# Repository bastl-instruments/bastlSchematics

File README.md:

# bastlSchematics
all hw design schematics in one place
license CC-BY-SA

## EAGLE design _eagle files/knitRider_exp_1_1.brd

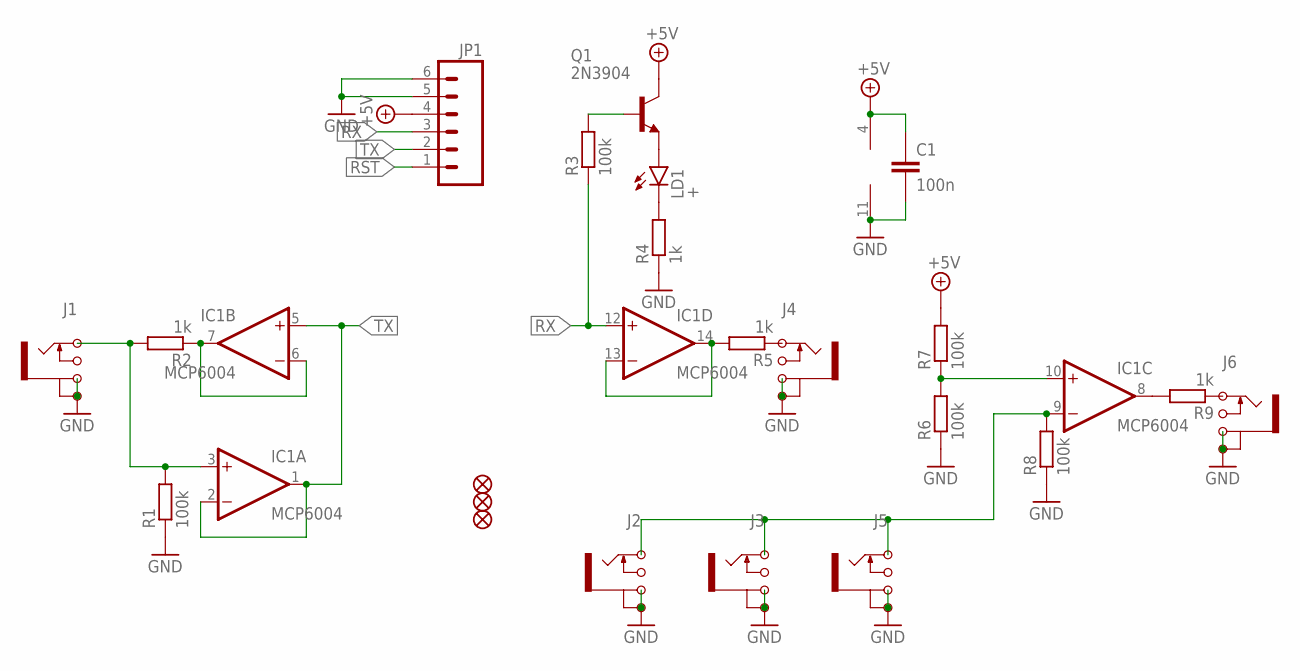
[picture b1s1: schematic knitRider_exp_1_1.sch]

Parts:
C1: 100n; CAPACITOR0603
FID1, FID2, FID3: FIDUCIAL
IC1: MCP6004; SO14
J1, J2, J3, J4, J5, J6: JACK_MONOJACK_MONO; JACK_MONO
JP1: M06LOCK; 1X06_LOCK
LD1: +; LEDSMALLHOLES
Q1: 2N3904; SOT23
R1, R3, R6, R7, R8: 100k; RESISTOR0603
R2, R4, R5, R9: 1k; RESISTOR0603

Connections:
+5V: C1.1, IC1.4 (V+), JP1.4, Q1.C, R7.2
GND: C1.2, IC1.11 (V-), J1.G1, J1.G2, J2.G1, J2.G2, J3.G1, J3.G2, J4.G1, J4.G2, J5.G1, J5.G2, J6.G1, J6.G2, JP1.5, JP1.6, R1.1, R4.1, R6.1, R8.1
unnamed: LD1.A, Q1.E
unnamed: Q1.B, R3.2
unnamed: J6.T, R9.1
unnamed: J4.T, R5.1
unnamed: IC1.6 (-IN), IC1.7 (OUT), R2.1
unnamed: IC1.9 (-IN), J2.T, J3.T, J5.T, R8.2
unnamed: IC1.10 (+IN), R6.2, R7.1
unnamed: LD1.K (C), R4.2
unnamed: IC1.3 (+IN), J1.T, R1.2, R2.2
unnamed: IC1.8 (OUT), R9.2
unnamed: IC1.13 (-IN), IC1.14 (OUT), R5.2
RST: JP1.1
RX: IC1.12 (+IN), JP1.3, R3.1
TX: IC1.1 (OUT), IC1.2 (-IN), IC1.5 (+IN), JP1.2

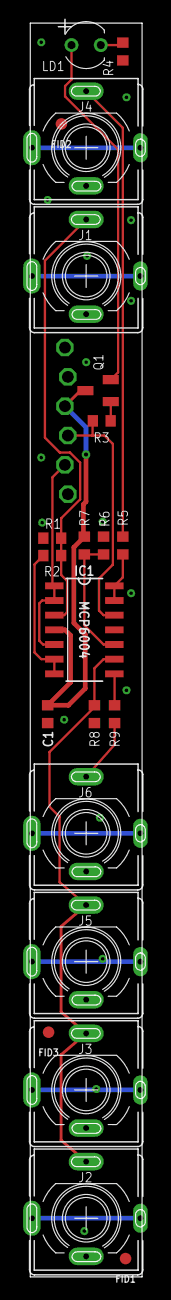
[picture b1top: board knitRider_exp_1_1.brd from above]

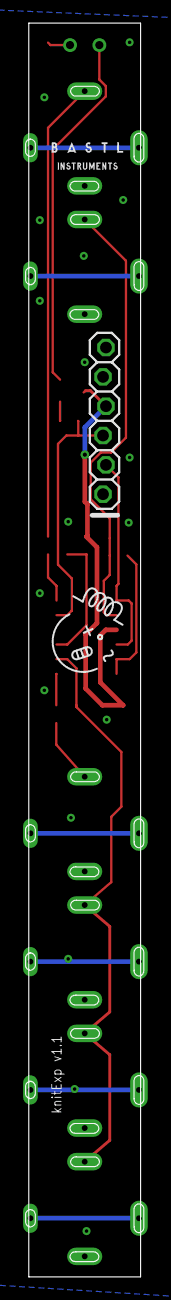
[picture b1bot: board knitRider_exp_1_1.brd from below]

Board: 2 copper layers, 10.2 x 108.6 mm, 25 parts (3 on the bottom side), 15 nets.

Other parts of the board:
U$1: BASTL_HLAVA_1
U$2: BASTL_LOGO_1

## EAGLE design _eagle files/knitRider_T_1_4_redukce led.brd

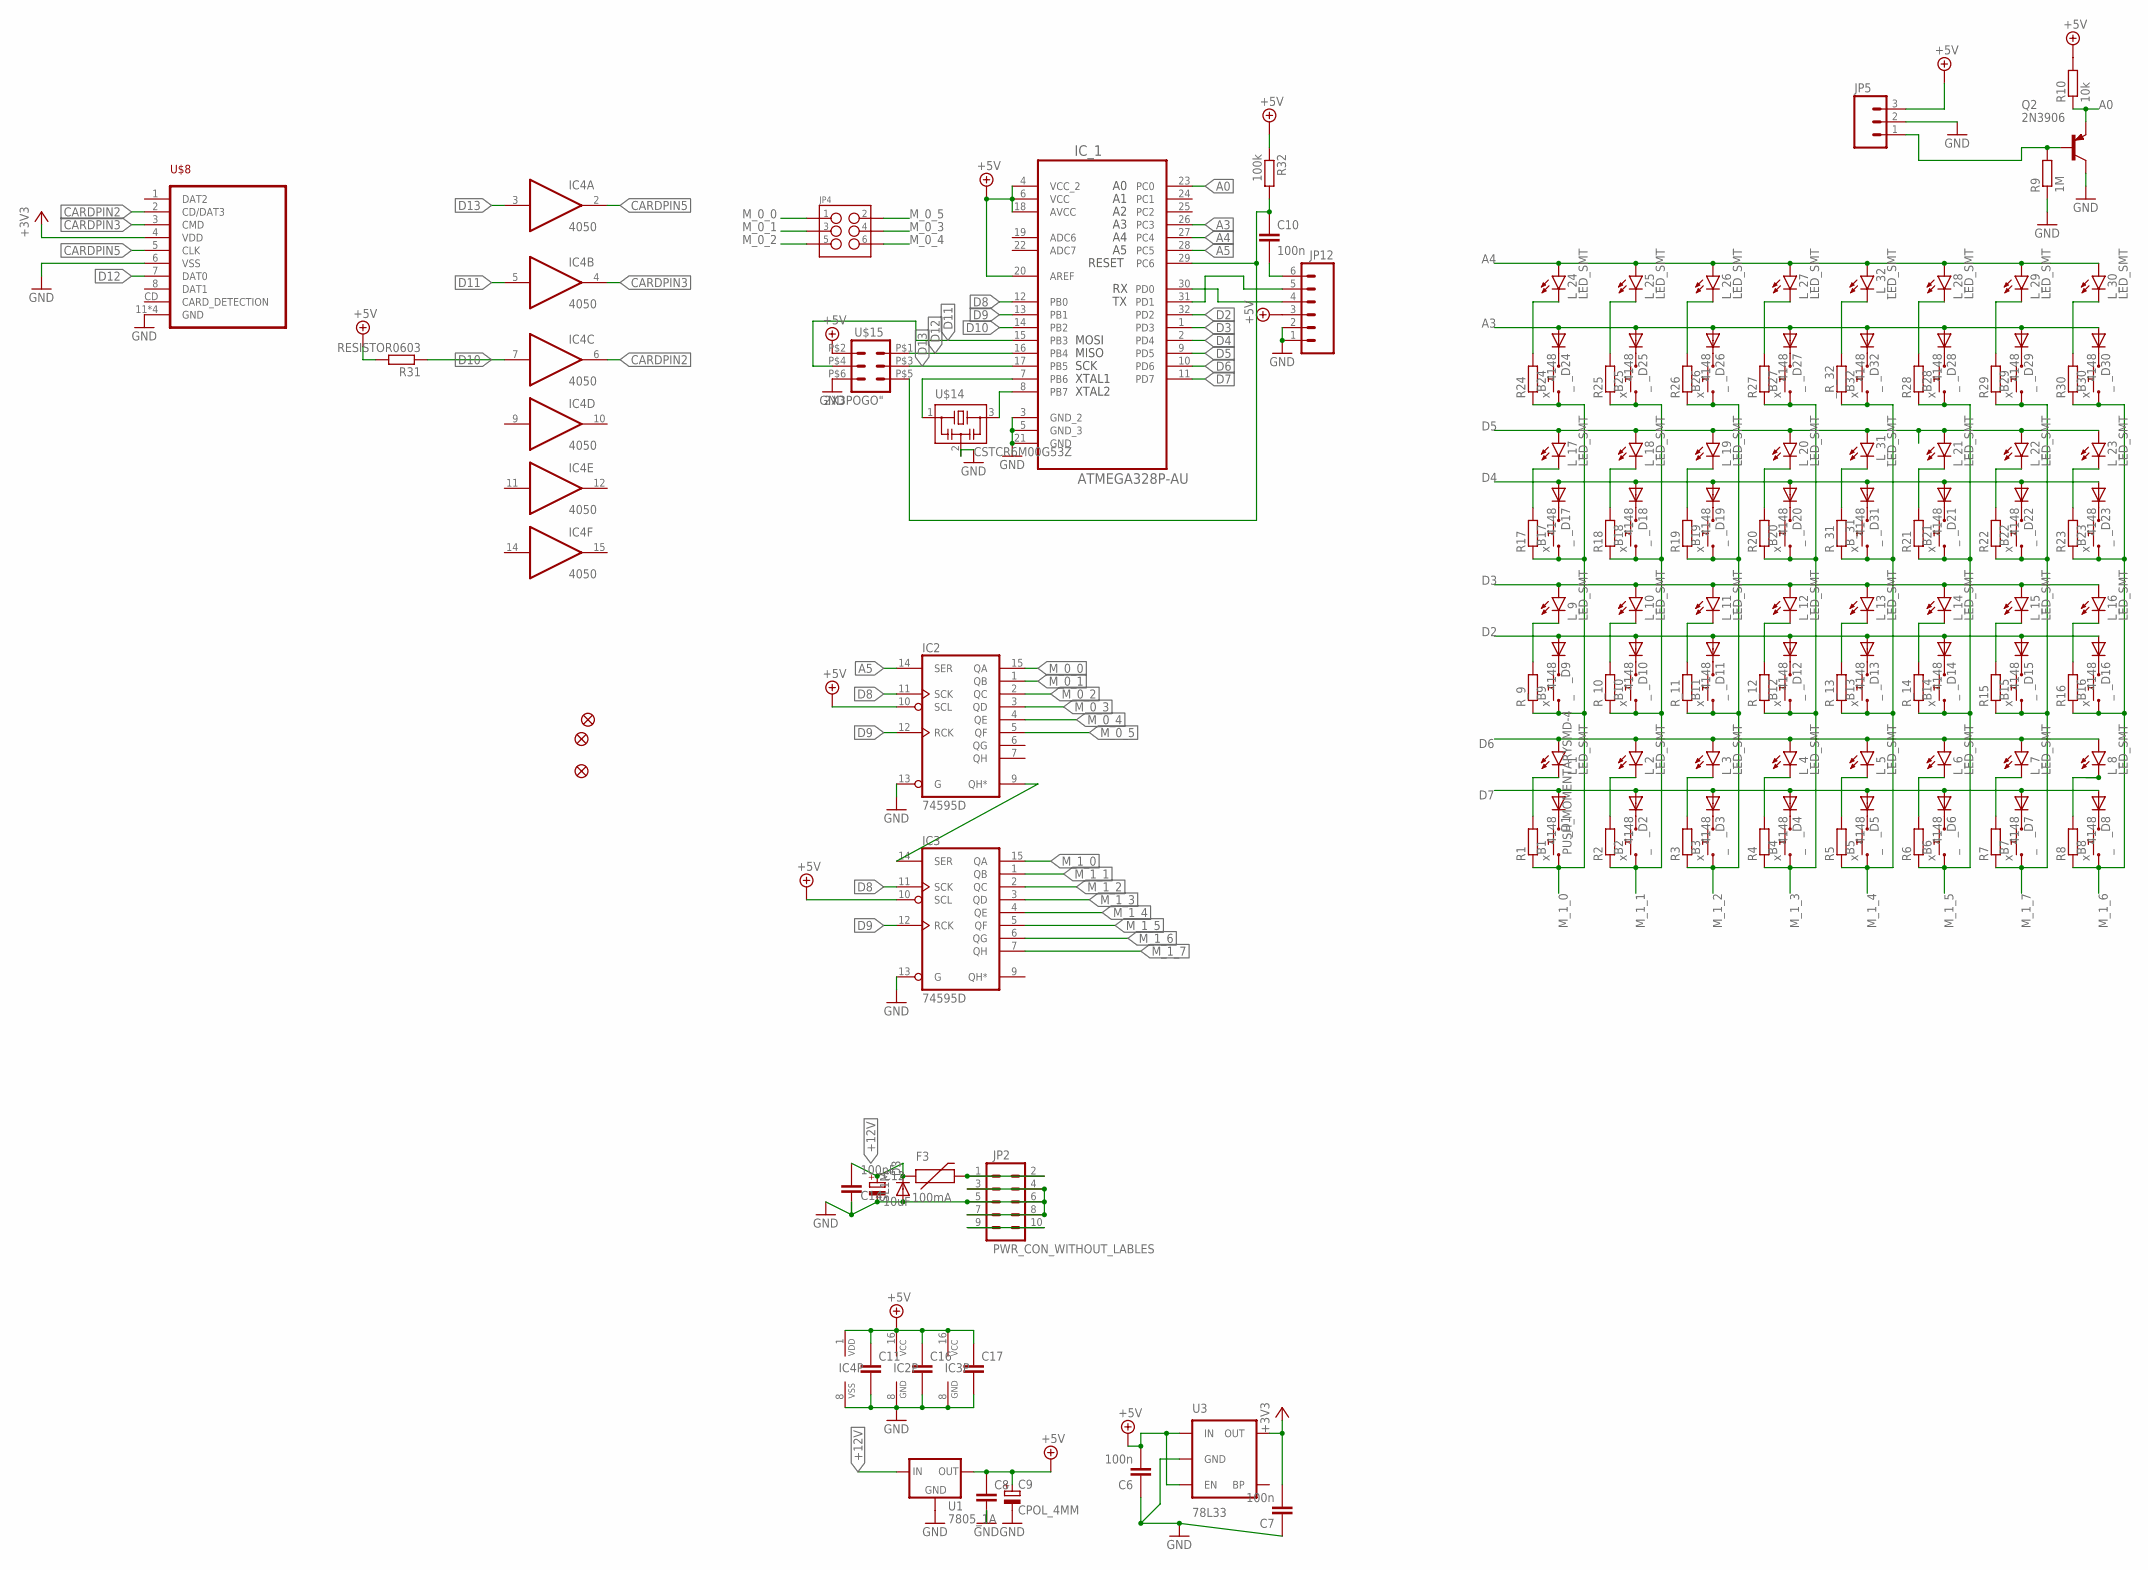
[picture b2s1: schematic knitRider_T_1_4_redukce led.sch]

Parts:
B1: PUSH_MOMENTARYSMD-4; TACTILE_SWITCH_TALL
B2, B3, B4, B5, B6, B7, B8, B9, B10, B11, B12, B13, B14, B15, B16, B17, B18, B19, B20, B21, B22, B23, B24, B25, B26, B27, B28, B29, B30, B32: _; TACTILE_SWITCH_TALL
B_31: _; TACTILE_SWITCH_TALL
C6, C7, C10: 100n; CAPACITOR0603
C8, C11, C16, C17: CAPACITOR0603
C9: CPOL_4MM
C12: 10uF; CPOL_4MM
C14: 100nF; CAPACITOR0603
D3: SL1M; SOD123
F3: 100mA; PTC0805
FID1, FID2, FID3: FIDUCIAL
IC2, IC3: 74595D; SO16
IC4: 4050; SO16
IC_1: ATMEGA328P-AU; TQFP32
JP2: PWR_CON_WITHOUT_LABLES
JP4: M03X2NO_SILK; 2X3-NS
JP5: M03LOCK; 1X03_LOCK
JP12: M06LOCK; 1X06_LOCK
L_1, L_2, L_3, L_4, L_5, L_6, L_7, L_8, L_9, L_10, L_11, L_12, L_13, L_14, L_15, L_16, L_17, L_18, L_19, L_20, L_21, L_22, L_23, L_24, L_25, L_26, L_27, L_28, L_29, L_30: LED_SMT; LED_0603
Q2: 2N3906; SOT23
R1, R2, R3, R4, R5, R6, R7, R8, R15, R16, R17, R18, R19, R20, R21, R22, R23, R24, R25, R26, R27, R28, R29, R30: x; RESISTOR0603
R9: 1M; RESISTOR0603
R10: 10k; RESISTOR0603
R31: RESISTOR0603
R32: 100k; RESISTOR0603
R_9, R_10, R_11, R_12, R_13, R_14, R_31: x; RESISTOR0603
U1: 7805_1A; DPAK
U3: 78L33; SOT23-5
U$8: SD_CARD_SLOT; MICRO_SD_CARD_SLOT
U$14: CSTCR6M00G53Z; CSTCR6M
U$15: 2X3POGO"; 2X3_POGO
_D1, _D2, _D3, _D4, _D5, _D6, _D7, _D8, _D9, _D10, _D11, _D12, _D13, _D14, _D15, _D16, _D17, _D18, _D19, _D20, _D21, _D22, _D23, _D24, _D25, _D26, _D27, _D28, _D29, _D30, _D31, _D32: 4148; DIODE_0603
_L_31, _L_32: LED_SMT; LED_0603
_R_32: x; RESISTOR0603

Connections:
+3V3: C7.2, U3.5 (OUT), U$8.4 (VDD)
+5V: C6.2, C8.1, C9.+, C11.1, C16.1, C17.1, IC2.10 (SCL), IC2.16 (VCC), IC3.10 (SCL), IC3.16 (VCC), IC4.1 (VDD), IC_1.4 (VCC_2), IC_1.6 (VCC), IC_1.18 (AVCC), IC_1.20 (AREF), JP5.3, JP12.3, R10.2, R31.2, R32.1, U1.3 (OUT), U3.1 (IN), U3.3 (EN), U$15.P$2 (2)
+12V: C12.+, C14.2, D3.C, F3.2 (1), U1.1 (IN)
A0: IC_1.23 (PC0), Q2.E, R10.1
A3: IC_1.26 (PC3), _D24.A, _D25.A, _D26.A, _D27.A, _D28.A, _D29.A, _D30.A, _D32.A
A4: IC_1.27 (PC4), L_24.A, L_25.A, L_26.A, L_27.A, L_28.A, L_29.A, L_30.A, _L_32.A
A5: IC2.14 (SER), IC_1.28 (PC5)
CARDPIN2: IC4.6 (O), U$8.2 (CD/DAT3)
CARDPIN3: IC4.4 (O), U$8.3 (CMD)
CARDPIN5: IC4.2 (O), U$8.5 (CLK)
D2: IC_1.32 (PD2), _D9.A, _D10.A, _D11.A, _D12.A, _D13.A, _D14.A, _D15.A, _D16.A
D3: IC_1.1 (PD3), L_9.A, L_10.A, L_11.A, L_12.A, L_13.A, L_14.A, L_15.A, L_16.A
D4: IC_1.2 (PD4), _D17.A, _D18.A, _D19.A, _D20.A, _D21.A, _D22.A, _D23.A, _D31.A
D5: IC_1.9 (PD5), L_17.A, L_18.A, L_19.A, L_20.A, L_21.A, L_22.A, L_23.A, _L_31.A
D6: IC_1.10 (PD6), L_1.A, L_2.A, L_3.A, L_4.A, L_5.A, L_6.A, L_7.A, L_8.A
D7: IC_1.11 (PD7), _D1.A, _D2.A, _D3.A, _D4.A, _D5.A, _D6.A, _D7.A, _D8.A
D8: IC2.11 (SCK), IC3.11 (SCK), IC_1.12 (PB0)
D9: IC2.12 (RCK), IC3.12 (RCK), IC_1.13 (PB1)
D10: IC4.7 (I), IC_1.14 (PB2), R31.1
D11: IC4.5 (I), IC_1.15 (PB3), U$15.P$4 (4)
D12: IC_1.16 (PB4), U$8.7 (DAT0), U$15.P$1 (1)
D13: IC4.3 (I), IC_1.17 (PB5), U$15.P$3 (3)
GND: C6.1, C7.1, C8.2, C9.-, C11.2, C12.-, C14.1, C16.2, C17.2, D3.A, IC2.8 (GND), IC2.13 (G), IC3.8 (GND), IC3.13 (G), IC4.8 (VSS), IC_1.3 (GND_2), IC_1.5 (GND_3), IC_1.21 (GND), JP2.3, JP2.4, JP2.5, JP2.6, JP2.7, JP2.8, JP5.2, JP12.1, JP12.2, Q2.C, R9.1, U1.4 (GND), U3.2 (GND), U$8.6 (VSS), U$8.11 (GND), U$8.12 (GND), U$8.13 (GND), U$8.G (GND), U$14.2, U$15.P$6 (6)
L32: R_31.2, _L_31.K (C)
M_0_0: IC2.15 (QA), JP4.1
M_0_1: IC2.1 (QB), JP4.3
M_0_2: IC2.2 (QC), JP4.5
M_0_3: IC2.3 (QD), JP4.4
M_0_4: IC2.4 (QE), JP4.6
M_0_5: IC2.5 (QF), JP4.2
M_1_0: B1.A1 (1), B1.A2 (1), B9.A1 (1), B9.A2 (1), B17.A1 (1), B17.A2 (1), B24.A1 (1), B24.A2 (1), IC3.15 (QA), R1.1, R17.1, R24.1, R_9.1
M_1_1: B2.A1 (1), B2.A2 (1), B10.A1 (1), B10.A2 (1), B18.A1 (1), B18.A2 (1), B25.A1 (1), B25.A2 (1), IC3.1 (QB), R2.1, R18.1, R25.1, R_10.1
M_1_2: B3.A1 (1), B3.A2 (1), B11.A1 (1), B11.A2 (1), B19.A1 (1), B19.A2 (1), B26.A1 (1), B26.A2 (1), IC3.2 (QC), R3.1, R19.1, R26.1, R_11.1
M_1_3: B4.A1 (1), B4.A2 (1), B12.A1 (1), B12.A2 (1), B20.A1 (1), B20.A2 (1), B27.A1 (1), B27.A2 (1), IC3.3 (QD), R4.1, R20.1, R27.1, R_12.1
M_1_4: B5.A1 (1), B5.A2 (1), B13.A1 (1), B13.A2 (1), B32.A1 (1), B32.A2 (1), B_31.A1 (1), B_31.A2 (1), IC3.4 (QE), R5.1, R_13.1, R_31.1, _R_32.1
M_1_5: B6.A1 (1), B6.A2 (1), B14.A1 (1), B14.A2 (1), B21.A1 (1), B21.A2 (1), B28.A1 (1), B28.A2 (1), IC3.5 (QF), R6.1, R21.1, R28.1, R_14.1
M_1_6: B8.A1 (1), B8.A2 (1), B16.A1 (1), B16.A2 (1), B23.A1 (1), B23.A2 (1), B30.A1 (1), B30.A2 (1), IC3.6 (QG), R8.1, R16.1, R23.1, R30.1
M_1_7: B7.A1 (1), B7.A2 (1), B15.A1 (1), B15.A2 (1), B22.A1 (1), B22.A2 (1), B29.A1 (1), B29.A2 (1), IC3.7 (QH), R7.1, R15.1, R22.1, R29.1
unnamed: B1.B1 (2), B1.B2 (2), _D1.K (C)
unnamed: B2.B1 (2), B2.B2 (2), _D2.K (C)
unnamed: B3.B1 (2), B3.B2 (2), _D3.K (C)
unnamed: JP5.1, Q2.B, R9.2
unnamed: B4.B1 (2), B4.B2 (2), _D4.K (C)
unnamed: B5.B1 (2), B5.B2 (2), _D5.K (C)
unnamed: B6.B1 (2), B6.B2 (2), _D6.K (C)
unnamed: L_3.K (C), R3.2
unnamed: F3.3 (2), JP2.1, JP2.2
unnamed: B9.B1 (2), B9.B2 (2), _D9.K (C)
unnamed: B10.B1 (2), B10.B2 (2), _D10.K (C)
unnamed: B7.B1 (2), B7.B2 (2), _D7.K (C)
unnamed: B8.B1 (2), B8.B2 (2), _D8.K (C)
unnamed: JP2.9, JP2.10
unnamed: B11.B1 (2), B11.B2 (2), _D11.K (C)
unnamed: L_4.K (C), R4.2
unnamed: L_5.K (C), R5.2
unnamed: L_6.K (C), R6.2
unnamed: L_7.K (C), R7.2
unnamed: B12.B1 (2), B12.B2 (2), _D12.K (C)
unnamed: L_8.K (C), R8.2
unnamed: B13.B1 (2), B13.B2 (2), _D13.K (C)
unnamed: B14.B1 (2), B14.B2 (2), _D14.K (C)
unnamed: B15.B1 (2), B15.B2 (2), _D15.K (C)
unnamed: B16.B1 (2), B16.B2 (2), _D16.K (C)
unnamed: B17.B1 (2), B17.B2 (2), _D17.K (C)
unnamed: B18.B1 (2), B18.B2 (2), _D18.K (C)
unnamed: B19.B1 (2), B19.B2 (2), _D19.K (C)
unnamed: L_1.K (C), R1.2
unnamed: L_2.K (C), R2.2
unnamed: B20.B1 (2), B20.B2 (2), _D20.K (C)
unnamed: B21.B1 (2), B21.B2 (2), _D21.K (C)
unnamed: B22.B1 (2), B22.B2 (2), _D22.K (C)
unnamed: B23.B1 (2), B23.B2 (2), _D23.K (C)
unnamed: B24.B1 (2), B24.B2 (2), _D24.K (C)
unnamed: L_9.K (C), R_9.2
unnamed: L_10.K (C), R_10.2
unnamed: L_11.K (C), R_11.2
unnamed: L_12.K (C), R_12.2
unnamed: L_13.K (C), R_13.2
unnamed: L_14.K (C), R_14.2
unnamed: L_15.K (C), R15.2
unnamed: L_16.K (C), R16.2
unnamed: B25.B1 (2), B25.B2 (2), _D25.K (C)
unnamed: B26.B1 (2), B26.B2 (2), _D26.K (C)
unnamed: L_18.K (C), R18.2
unnamed: L_19.K (C), R19.2
unnamed: L_17.K (C), R17.2
unnamed: L_20.K (C), R20.2
unnamed: L_23.K (C), R23.2
unnamed: L_22.K (C), R22.2
unnamed: B27.B1 (2), B27.B2 (2), _D27.K (C)
unnamed: L_21.K (C), R21.2
unnamed: B28.B1 (2), B28.B2 (2), _D28.K (C)
unnamed: B29.B1 (2), B29.B2 (2), _D29.K (C)
unnamed: B30.B1 (2), B30.B2 (2), _D30.K (C)
unnamed: B_31.B1 (2), B_31.B2 (2), _D31.K (C)
unnamed: B32.B1 (2), B32.B2 (2), _D32.K (C)
unnamed: IC2.9 (QH*), IC3.14 (SER)
unnamed: L_24.K (C), R24.2
unnamed: L_25.K (C), R25.2
unnamed: L_26.K (C), R26.2
unnamed: L_27.K (C), R27.2
unnamed: L_28.K (C), R28.2
unnamed: L_29.K (C), R29.2
unnamed: L_30.K (C), R30.2
unnamed: IC_1.7 (PB6), U$14.1
unnamed: IC_1.8 (PB7), U$14.3
unnamed: IC_1.30 (PD0), JP12.4
unnamed: IC_1.31 (PD1), JP12.5
unnamed: C10.1, IC_1.29 (PC6), R32.2, U$15.P$5 (5)
unnamed: C10.2, JP12.6
_L32: _L_32.K (C), _R_32.2

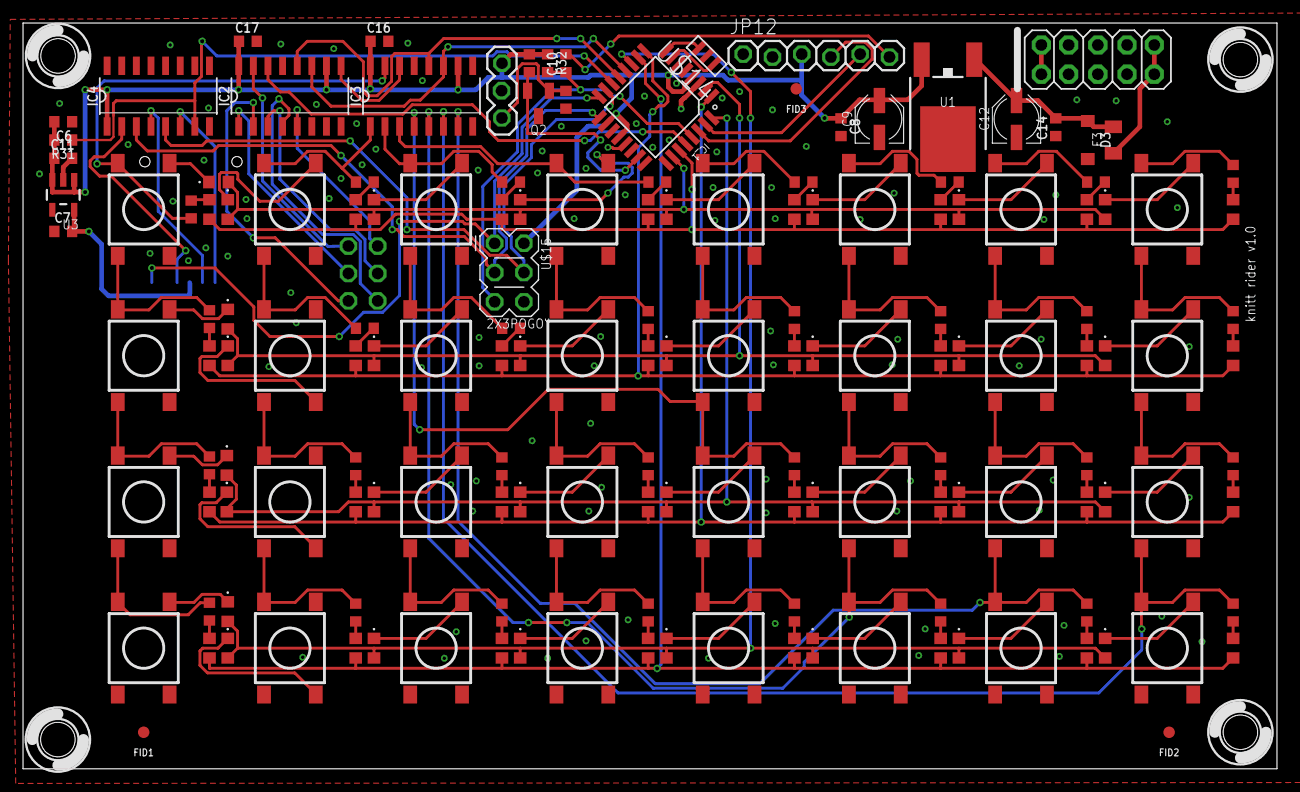
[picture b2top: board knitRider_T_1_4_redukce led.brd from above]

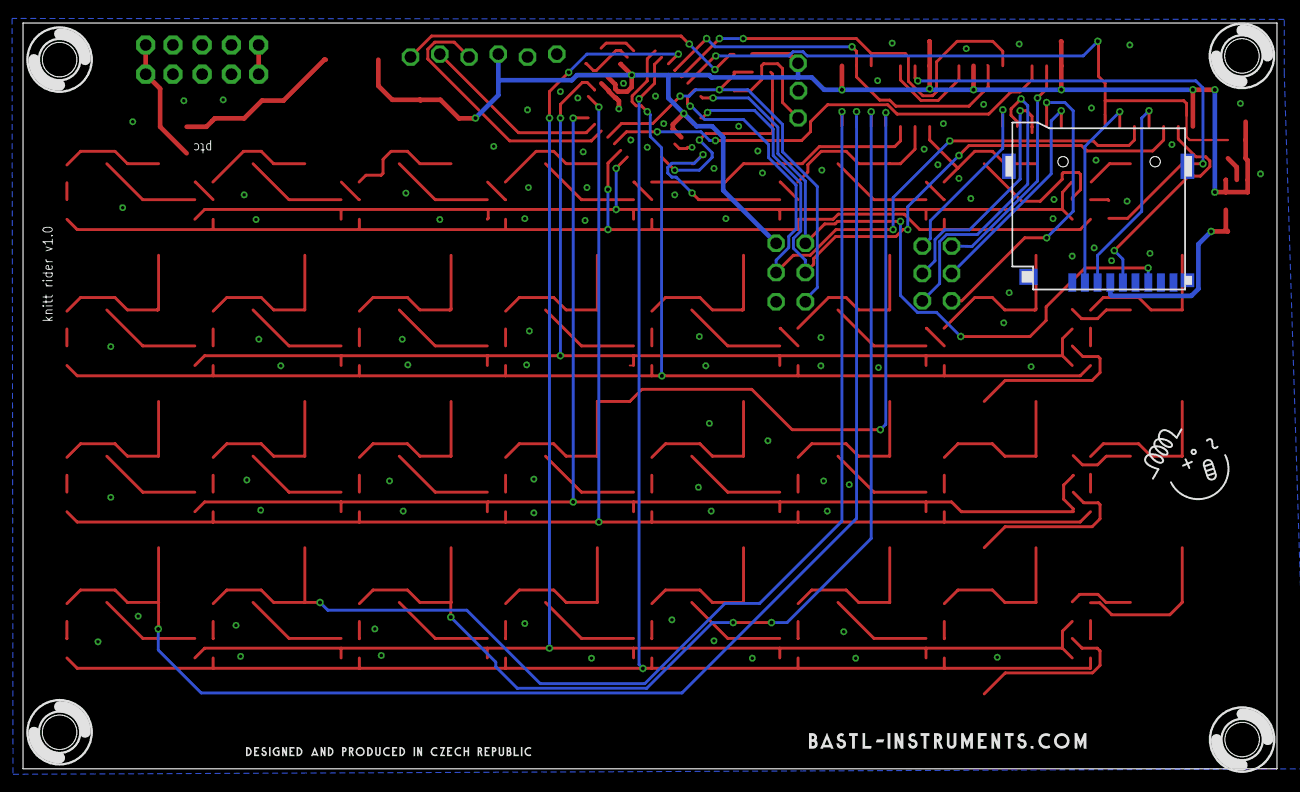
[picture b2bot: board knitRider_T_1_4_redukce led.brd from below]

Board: 2 copper layers, 108.9 x 64.8 mm, 168 parts (4 on the bottom side), 111 nets.

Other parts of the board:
U$1: BASTL_WEB_2
U$2, U$3, U$4, U$5: 3MM_HOLE
U$6: DES_PROD
U$11: BASTL_HLAVA_1

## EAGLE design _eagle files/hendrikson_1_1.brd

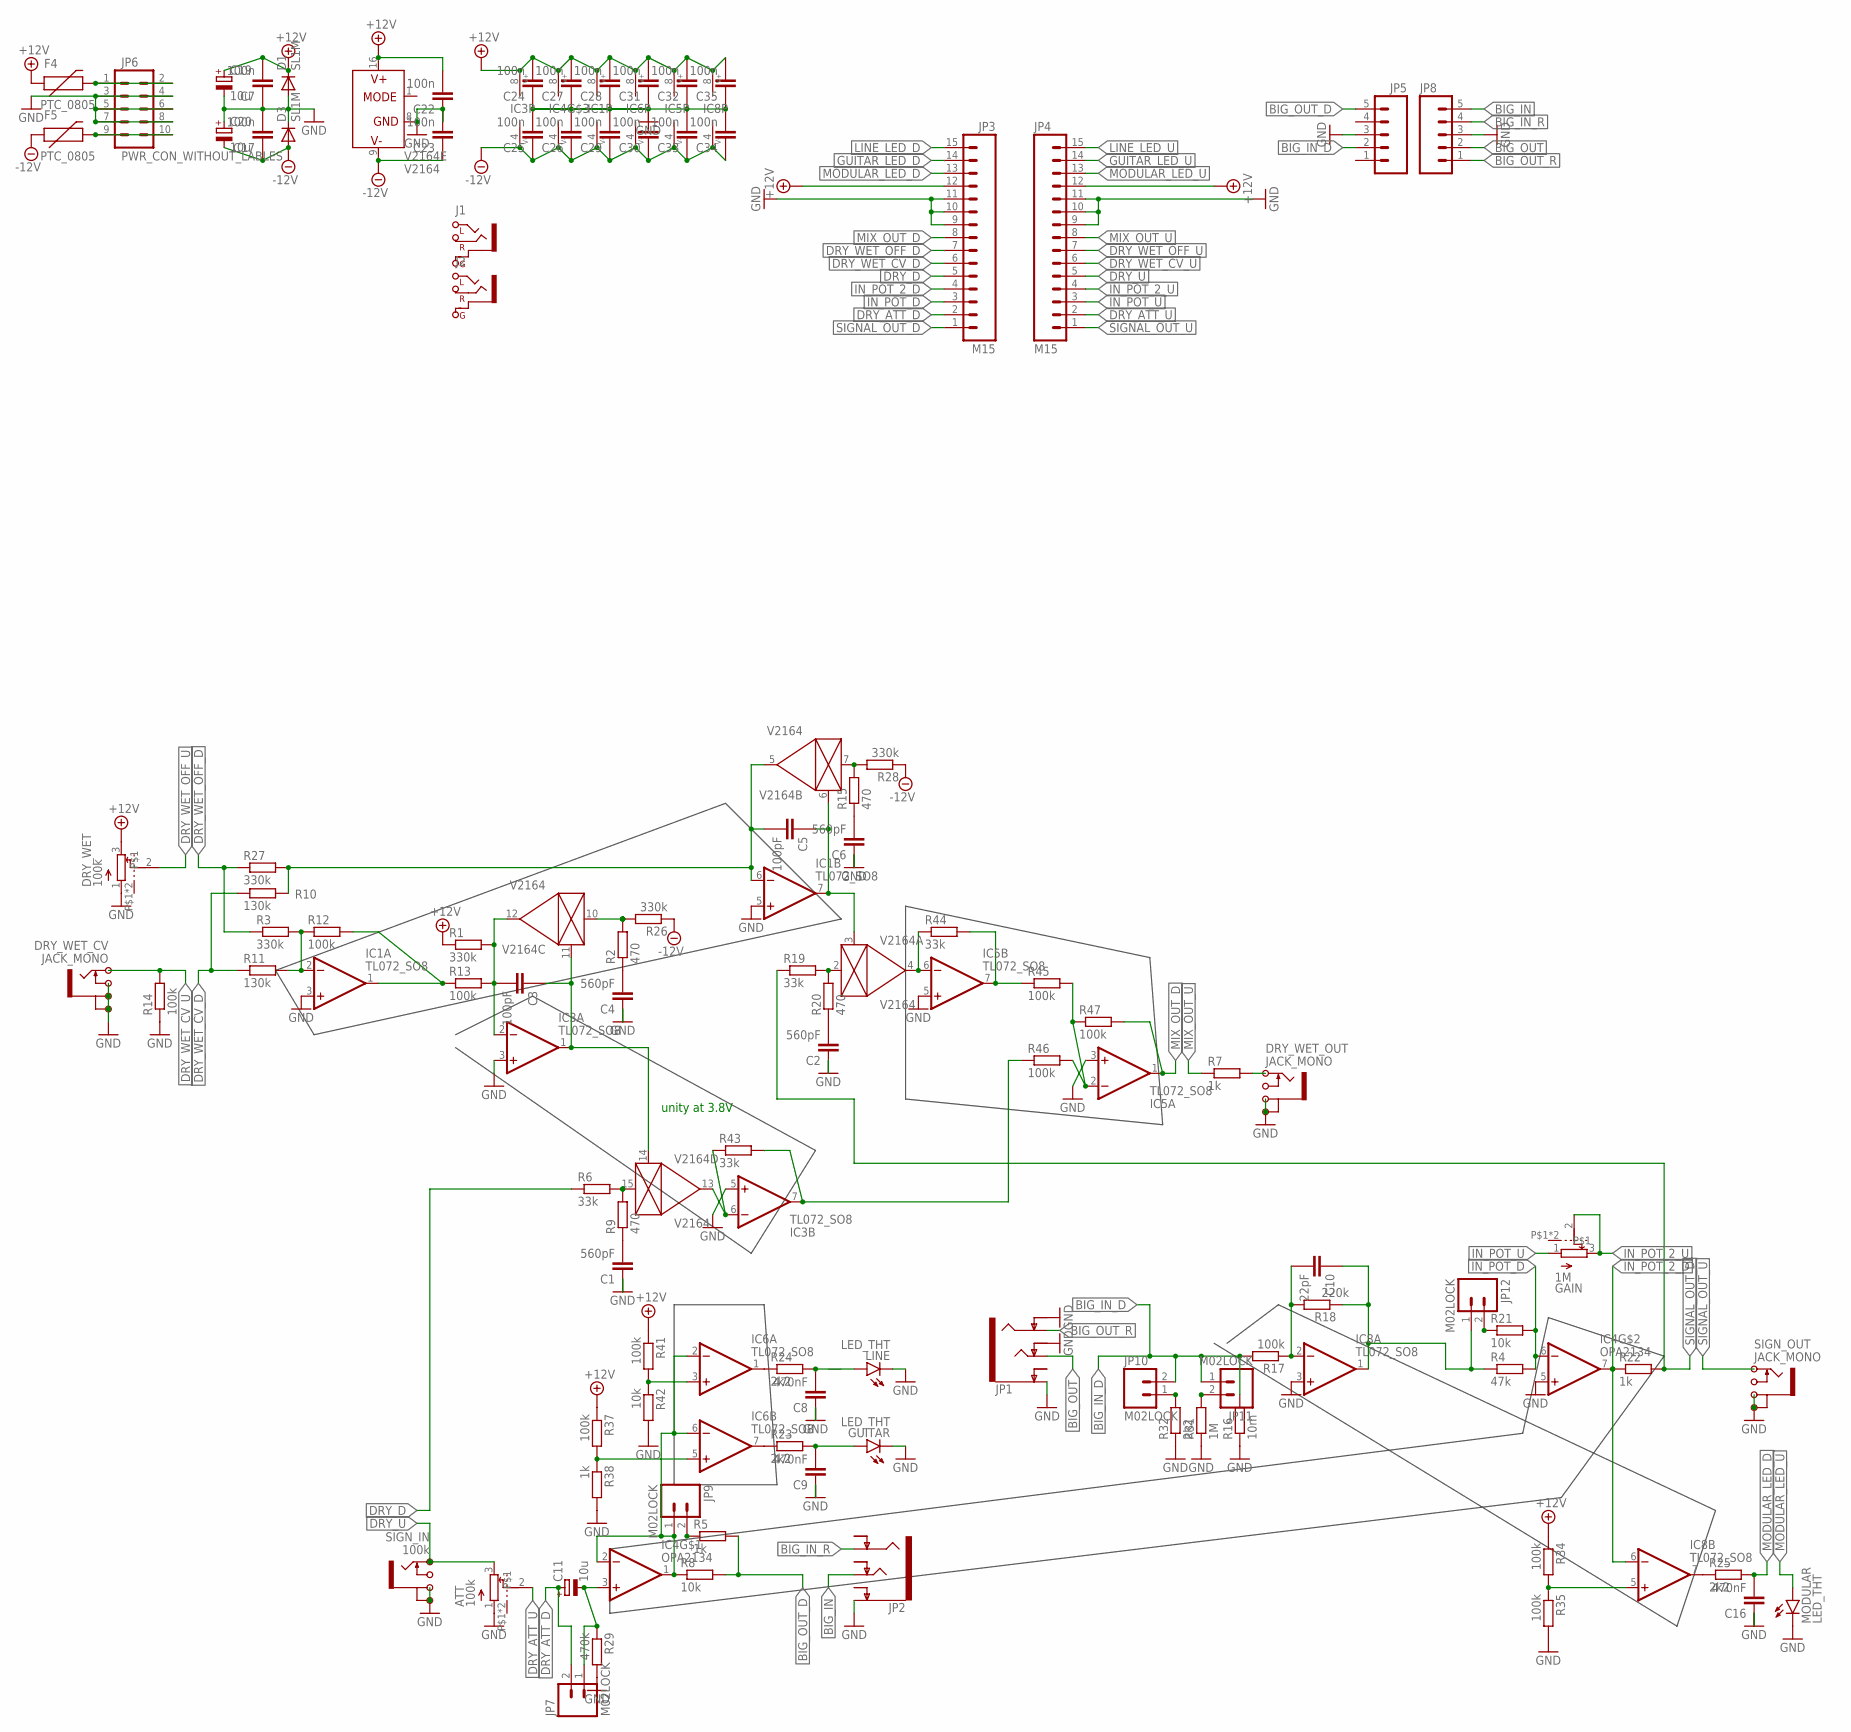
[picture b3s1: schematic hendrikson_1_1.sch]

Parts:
ATT: 100k; POT_ALPHA
C1, C2, C4, C6: 560pF; CAPACITOR0603
C3, C5: 100pF; CAPACITOR0603
C7, C17, C22, C23, C24, C25, C26, C27, C28, C29, C30, C31, C32, C33, C34, C35: 100n; CAPACITOR0603
C8, C9, C16: 470nF; CAPACITOR0603
C10: 22pF; CAPACITOR0603
C11, C19, C20: 10u; CPOL_4MM
D1, D3: SL1M; SOD123
DRY_WET: 100k; POT_ALPHA
DRY_WET_CV: JACK_MONO
DRY_WET_OUT: JACK_MONO
F4, F5: PTC_0805; PTC0805
GAIN: 1M; POT_ALPHA
GUITAR: LED_THT; LEDSMALLHOLES
IC1, IC3, IC5, IC6, IC8: TL072_SO8; SO8
IC4: OPA2134; SO8
J1, J2: NEUTRIK_VERT_JACK_6.3MM; RJ5VM
JP1, JP2: SPARKFUN-CONNECTORS_AUDIO-JACK4-.25-HORIZ-TRS; SPARKFUN-CONNECTORS_AUDIO-JACK-.25-INCH-HORIZ-PTH
JP3, JP4: M15; 1X15
JP5: M05PTH; 1X05
JP6: PWR_CON_WITHOUT_LABLES
JP7, JP9, JP10, JP11, JP12: M02LOCK; 1X02_LOCK
JP8: M05PTH_LONGPADS; 1X05_LONGPADS
LINE: LED_THT; LEDSMALLHOLES
MODULAR: LED_THT; LEDSMALLHOLES
R1, R3, R26, R27, R28: 330k; RESISTOR0603
R2, R9, R15, R20: 470; RESISTOR0603
R4: 47k; RESISTOR0603
R5, R7, R22, R38: 1k; RESISTOR0603
R6, R19, R43, R44: 33k; RESISTOR0603
R8, R21, R42: 10k; RESISTOR0603
R10, R11: 130k; RESISTOR0603
R12, R13, R14, R17, R34, R35, R37, R41, R45, R46, R47: 100k; RESISTOR0603
R16: 10m; RESISTOR0603
R18: 220k; RESISTOR0603
R23, R24, R25, R32: 2k2; RESISTOR0603
R29: 470k; RESISTOR0603
R31: 1M; RESISTOR0603
SIGN_IN: 100k; JACK_MONO
SIGN_OUT: JACK_MONO
V2164: V2164; SO16

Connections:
+12V: C7.2, C19.+, C22.2, C24.2, C27.2, C28.2, C31.2, C32.2, C35.2, D1.C, DRY_WET.3, F4.2 (1), IC1.8 (V+), IC3.8 (V+), IC4.8 (V+), IC5.8 (V+), IC6.8 (V+), IC8.8 (V+), JP3.12, JP4.12, R1.1, R34.1, R37.1, R41.1, V2164.16 (V+)
-12V: C17.1, C20.-, C23.1, C25.1, C26.1, C29.1, C30.1, C33.1, C34.1, D3.A, F5.2 (1), IC1.4 (V-), IC3.4 (V-), IC4.4 (V-), IC5.4 (V-), IC6.4 (V-), IC8.4 (V-), R26.1, R28.1, V2164.9 (V-)
BIG_IN: JP2.P$6 (TIP), JP8.5
BIG_IN_D: JP5.2, JP10.2, JP11.1, R16.2, R17.2
BIG_IN_R: JP2.P$4 (RING), JP8.4
BIG_OUT: JP1.P$6 (TIP), JP8.2
BIG_OUT_D: JP5.5, R5.2, R8.2
BIG_OUT_R: JP1.P$4 (RING), JP8.1
DRY_ATT_D: C11.+, JP3.2, JP7.2
DRY_ATT_U: ATT.2, JP4.2
DRY_D: JP3.5, R6.1
DRY_U: ATT.3, JP4.5, SIGN_IN.T
DRY_WET_CV_D: JP3.6, R10.1, R11.1
DRY_WET_CV_U: DRY_WET_CV.T, JP4.6, R14.2
DRY_WET_OFF_D: JP3.7, R3.1, R27.1
DRY_WET_OFF_U: DRY_WET.2, JP4.7
GND: ATT.1, C1.1, C2.1, C4.1, C6.1, C7.1, C8.1, C9.1, C16.1, C17.2, C19.-, C20.+, C22.1, C23.2, C24.1, C25.2, C26.2, C27.1, C28.1, C29.2, C30.2, C31.1, C32.1, C33.2, C34.2, C35.1, D1.A, D3.C, DRY_WET.1, DRY_WET_CV.G1, DRY_WET_CV.G2, DRY_WET_CV.SW, DRY_WET_OUT.G1, DRY_WET_OUT.G2, GUITAR.K (C), IC1.3 (+IN), IC1.5 (+IN), IC3.3 (+IN), IC3.5 (+IN), IC4.5 (+IN), IC5.3 (+IN), IC5.5 (+IN), IC8.3 (+IN), JP1.P$2 (EARTH), JP1.P$5 (RING-NORM), JP1.P$7 (TIP-NORM), JP2.P$2 (EARTH), JP3.9, JP3.10, JP3.11, JP4.9, JP4.10, JP4.11, JP5.3, JP6.3, JP6.4, JP6.5, JP6.6, JP6.7, JP6.8, JP8.3, LINE.K (C), MODULAR.K (C), R14.1, R16.1, R29.2, R31.1, R32.1, R35.2, R38.2, R42.2, SIGN_IN.G1, SIGN_IN.G2, SIGN_OUT.G1, SIGN_OUT.G2, V2164.8 (GND)
GUITAR_LED_D: JP3.14
GUITAR_LED_U: C9.2, GUITAR.A, JP4.14, R23.2
IN_POT_2_D: IC4.7 (OUT), IC8.6 (-IN), JP3.4, R22.1
IN_POT_2_U: GAIN.2, GAIN.3, JP4.4
IN_POT_D: IC4.6 (-IN), JP3.3, R4.2, R21.2
IN_POT_U: GAIN.1, JP4.3
LINE_LED_D: JP3.15
LINE_LED_U: C8.2, JP4.15, LINE.A, R24.2
MIX_OUT_D: IC5.1 (OUT), JP3.8, R47.2
MIX_OUT_U: JP4.8, R7.1
MODULAR_LED_D: C16.2, JP3.13, R25.2
MODULAR_LED_U: JP4.13, MODULAR.A
unnamed: IC6.1 (OUT), R24.1
unnamed: IC8.7 (OUT), R25.1
unnamed: IC1.1 (OUT), R12.2, R13.1
unnamed: C4.2, R2.1
unnamed: IC6.7 (OUT), R23.1
unnamed: C3.1, IC3.1 (OUT), V2164.11 (CTRL), V2164.14 (CTRL)
unnamed: C11.-, IC4.3 (+IN), JP7.1, R29.1
unnamed: JP12.2, R21.1
unnamed: IC4.1 (OUT), IC4.2 (-IN), IC6.2 (-IN), IC6.6 (-IN), JP9.1, R8.1
unnamed: R6.2, R9.2, V2164.15 (IN)
unnamed: C1.2, R9.1
unnamed: IC3.6 (-IN), R43.1, V2164.13 (OUT)
unnamed: IC3.7 (OUT), R43.2, R46.1
unnamed: IC5.7 (OUT), R44.2, R45.1
unnamed: IC5.6 (-IN), R44.1, V2164.4 (OUT)
unnamed: C5.1, IC1.7 (OUT), V2164.3 (CTRL), V2164.6 (CTRL)
unnamed: R15.2, R28.2, V2164.7 (IN)
unnamed: IC5.2 (-IN), R45.2, R46.2, R47.1
unnamed: C10.2, IC8.2 (-IN), R17.1, R18.2
unnamed: R19.2, R20.2, V2164.2 (IN)
unnamed: C2.2, R20.1
unnamed: JP9.2, R5.1
unnamed: DRY_WET_OUT.T, R7.2
unnamed: R2.2, R26.2, V2164.10 (IN)
unnamed: IC1.2 (-IN), R3.2, R11.2, R12.1
unnamed: C6.2, R15.1
unnamed: IC8.5 (+IN), R34.2, R35.1
unnamed: JP10.1, R32.2
unnamed: JP11.2, R31.2
unnamed: F4.3 (2), JP6.1, JP6.2
unnamed: F5.3 (2), JP6.9, JP6.10
unnamed: IC6.5 (+IN), R37.2, R38.1
unnamed: IC6.3 (+IN), R41.2, R42.1
SIGNAL_OUT_D: JP3.1, R19.1, R22.2
SIGNAL_OUT_U: JP4.1, SIGN_OUT.T
VCA_IN_SUM_D: C5.2, IC1.6 (-IN), R10.2, R27.2, V2164.5 (OUT)
VCA_OUT_SUM_D: C3.2, IC3.2 (-IN), R1.2, R13.2, V2164.12 (OUT)
WHATEVR: C10.1, IC8.1 (OUT), JP12.1, R4.1, R18.1

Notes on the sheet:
unity at 3.8V

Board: 2 copper layers, 107 parts (87 on the bottom side), 65 nets, no tracks yet.

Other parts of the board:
U$1: 3MM_HOLE

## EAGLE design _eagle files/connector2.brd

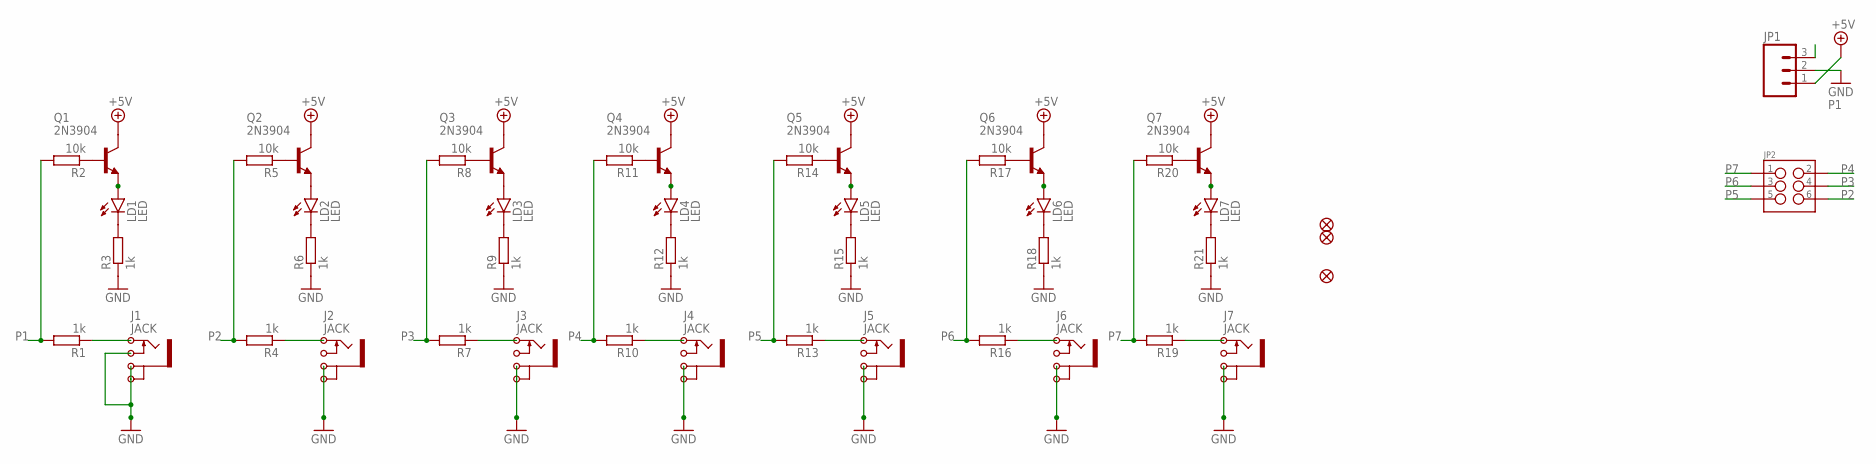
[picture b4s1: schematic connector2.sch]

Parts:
FID1, FID2, FID3: FIDUCIAL
J1, J2, J3, J4, J5, J6, J7: JACK; JACK_MONO
JP1: M03LOCK; 1X03_LOCK
JP2: M03X2NO_SILK; 2X3-NS
LD1, LD2, LD3, LD4, LD5, LD6, LD7: LED; LEDSMALLHOLES
Q1, Q2, Q3, Q4, Q5, Q6, Q7: 2N3904; SOT23
R1, R3, R4, R6, R7, R9, R10, R12, R13, R15, R16, R18, R19, R21: 1k; RESISTOR0603
R2, R5, R8, R11, R14, R17, R20: 10k; RESISTOR0603

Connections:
+5V: JP1.1, Q1.C, Q2.C, Q3.C, Q4.C, Q5.C, Q6.C, Q7.C
GND: J1.G1, J1.G2, J1.SW, J2.G1, J2.G2, J3.G1, J3.G2, J4.G1, J4.G2, J5.G1, J5.G2, J6.G1, J6.G2, J7.G1, J7.G2, JP1.2, R3.1, R6.1, R9.1, R12.1, R15.1, R18.1, R21.1
unnamed: LD3.K (C), R9.2
unnamed: Q1.B, R2.1
unnamed: LD2.K (C), R6.2
unnamed: J3.T, R7.1
unnamed: J2.T, R4.1
unnamed: LD4.A, Q4.E
unnamed: LD3.A, Q3.E
unnamed: LD4.K (C), R12.2
unnamed: LD5.A, Q5.E
unnamed: J4.T, R10.1
unnamed: LD5.K (C), R15.2
unnamed: J5.T, R13.1
unnamed: LD6.A, Q6.E
unnamed: LD6.K (C), R18.2
unnamed: J6.T, R16.1
unnamed: LD7.A, Q7.E
unnamed: J1.T, R1.1
unnamed: LD7.K (C), R21.2
unnamed: J7.T, R19.1
unnamed: Q2.B, R5.1
unnamed: LD2.A, Q2.E
unnamed: Q3.B, R8.1
unnamed: Q4.B, R11.1
unnamed: Q5.B, R14.1
unnamed: LD1.A, Q1.E
unnamed: LD1.K (C), R3.2
unnamed: Q6.B, R17.1
unnamed: Q7.B, R20.1
P1: JP1.3, R1.2, R2.2
P2: JP2.6, R4.2, R5.2
P3: JP2.4, R7.2, R8.2
P4: JP2.2, R10.2, R11.2
P5: JP2.5, R13.2, R14.2
P6: JP2.3, R16.2, R17.2
P7: JP2.1, R19.2, R20.2

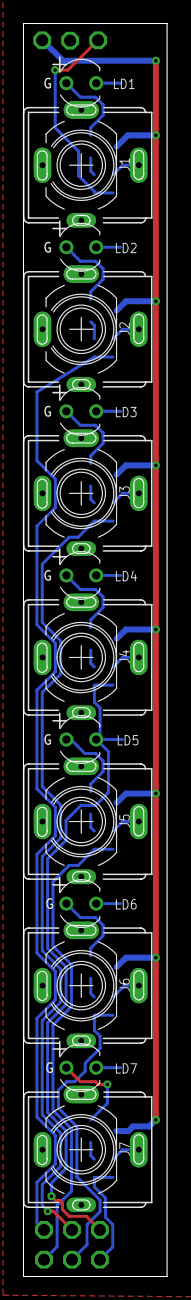
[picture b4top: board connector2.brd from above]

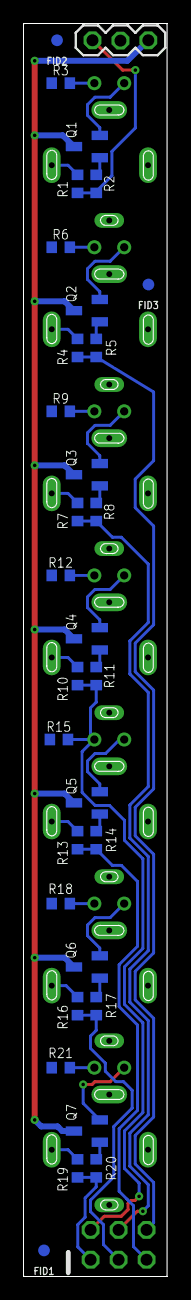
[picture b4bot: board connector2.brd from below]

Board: 2 copper layers, 12.2 x 106.7 mm, 47 parts (33 on the bottom side), 37 nets.

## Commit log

2018-04-03 added all schematics in pdf and png to one repository
2018-10-04 ADDED MORE SCHEMATICS
2020-03-17 added dirty skis2 schematics
2024-11-28 Upload older schematics and boards
    Upload older schematics and boards

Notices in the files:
parts and their libraries:
SparkFun-Connectors: Licensing: Creative Commons ShareAlike 4.0 International - https://creativecommons.org/licenses/by-sa/4.0
